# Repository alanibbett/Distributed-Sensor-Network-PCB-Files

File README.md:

# Distributed-Sensor-Network-PCB-Files
PCB files in eagle PCB format and Gerber for the sensor board of the DSN 
This repository contains the PCB design files for a simple raspberry PI expansion board. 
This design does not comply with the specifications of a RaspberryPi Hat but does support contain the following items:

*	OLED Display to indicate system status: the OLED provides a way to display a simple menu based user interface
*	RFM9x LoRa radio: Provides a network connection to LoRaWAN or other LoRa nodes
*	Global Position System GPS receiver: Allows the node to accurately collect UTC time and date as well as location information of other data captured (GPS)
*	DC power supply input connector: To supply regulated 5VDC to the system
*	LED: Status LED – shows system status at a glance
*	GPIO: 5 of the RaspberryPI GPIO pins have been broken out in a Signal-Voltage-Ground (SVG) layout for connecting to external devices. These can include relays, sensors, switches and so forth.
*	Keypad: A three button keypad for interacting with the OLED menu user interface.

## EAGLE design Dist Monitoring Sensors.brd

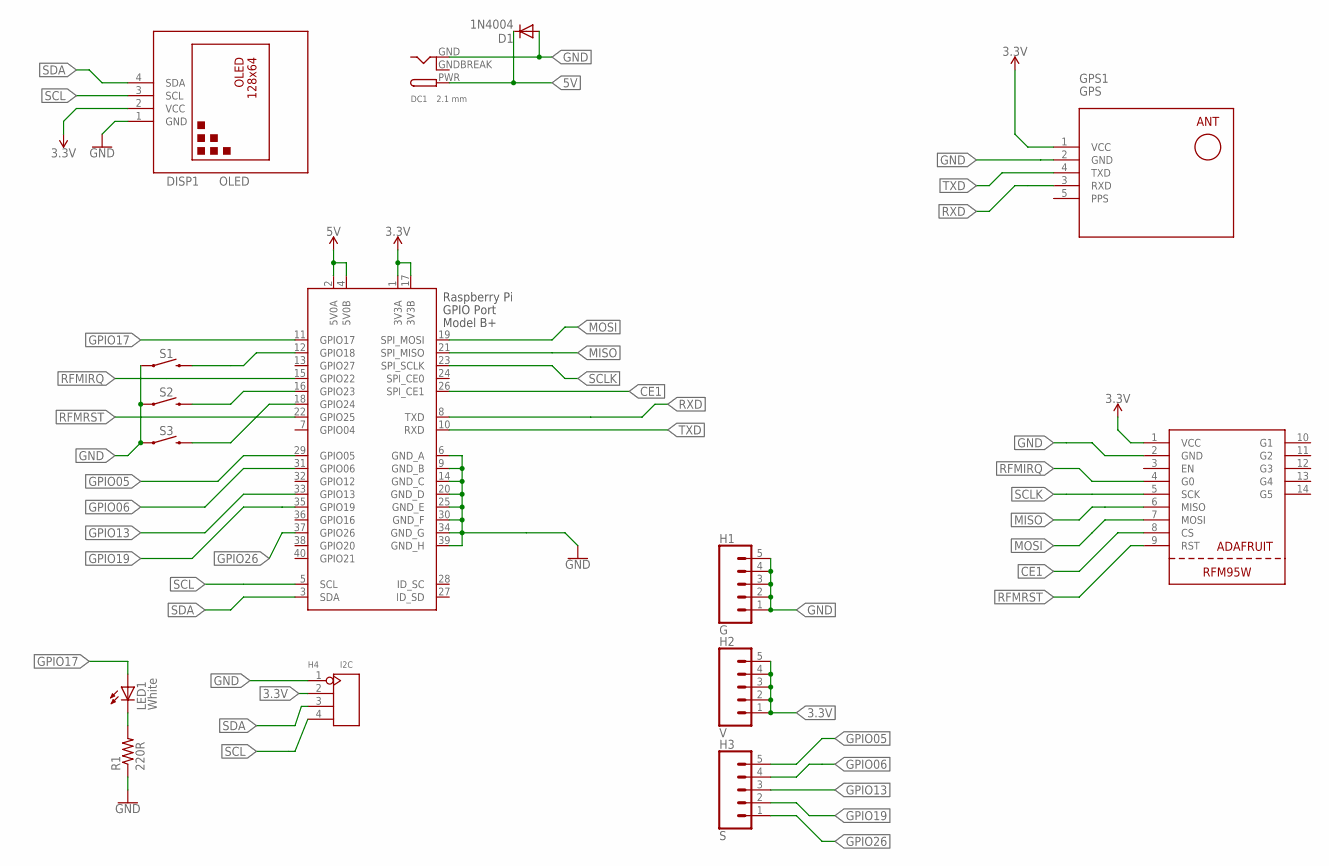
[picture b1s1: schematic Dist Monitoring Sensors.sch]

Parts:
D1: 1N4004; DO41-10
DC1: 2.1 mm; DCJACK_2MM_PTH
DISP1: OLED; DISPLAY-OLED-128X64-I2C
GPS1: GPS; GPS-RECEIVER-NEO6M-GENERIC
H1: G; 1X05
H2: V; 1X05
H3: S; 1X05
H4: I2C; H4-2.54
LED1: White; LED3MM
R1: 220R; 0207/10
S1, S2, S3: MOMENTARY-SWITCH-SPST-PTH-6.0MM; TACTILE_SWITCH_PTH_6.0MM
U1: RFM95W
X1: Raspi 40 Pin Connector; RASPI_BOARD_B+_EDGES_3DRILL_PAD

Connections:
3.3V: DISP1.2 (VCC), GPS1.1 (VCC), H2.1, H2.2, H2.3, H2.4, H2.5, H4.2, U1.1 (VCC), X1.1 (3V3A), X1.17 (3V3B)
5V: D1.C, DC1.PWR, X1.2 (5V0A), X1.4 (5V0B)
CE1: U1.8 (CS), X1.26 (SPI_CE1)
GND: D1.A, DC1.GND, DISP1.1 (GND), GPS1.2 (GND), H1.1, H1.2, H1.3, H1.4, H1.5, H4.1, R1.1, S1.1, S2.1, S3.1, U1.2 (GND), X1.6 (GND_A), X1.9 (GND_B), X1.14 (GND_C), X1.20 (GND_D), X1.25 (GND_E), X1.30 (GND_F), X1.34 (GND_G), X1.39 (GND_H)
GNDBREAK: DC1.GNDBREAK
GPIO05: H3.5, X1.29 (GPIO05)
GPIO06: H3.4, X1.31 (GPIO06)
GPIO13: H3.3, X1.33 (GPIO13)
GPIO17: LED1.A, X1.11 (GPIO17)
GPIO18: S1.3 (2), X1.12 (GPIO18)
GPIO19: H3.2, X1.35 (GPIO19)
GPIO23: S2.3 (2), X1.16 (GPIO23)
GPIO24: S3.3 (2), X1.18 (GPIO24)
GPIO26: H3.1, X1.37 (GPIO26)
MISO: U1.6 (MISO), X1.21 (SPI_MISO)
MOSI: U1.7 (MOSI), X1.19 (SPI_MOSI)
unnamed: LED1.K (C), R1.2
RFMIRQ: U1.4 (G0), X1.15 (GPIO22)
RFMRST: U1.9 (RST), X1.22 (GPIO25)
RXD: GPS1.3 (RXD), X1.8 (TXD)
SCL: DISP1.3 (SCL), H4.4, X1.5 (SCL)
SCLK: U1.5 (SCK), X1.23 (SPI_SCLK)
SDA: DISP1.4 (SDA), H4.3, X1.3 (SDA)
TXD: GPS1.4 (TXD), X1.10 (RXD)

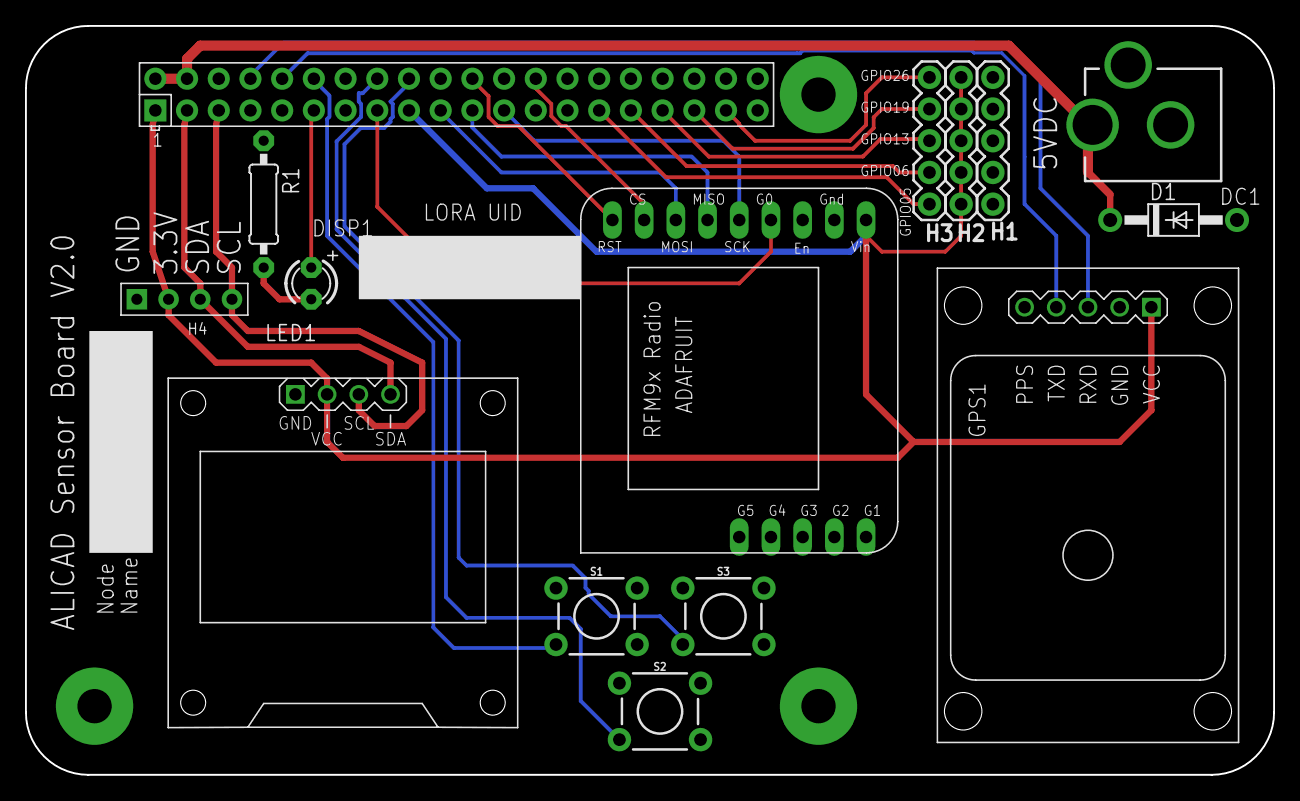
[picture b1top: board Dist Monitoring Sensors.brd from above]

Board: 2 copper layers, 100.0 x 60.0 mm, 15 parts (0 on the bottom side), 23 nets.

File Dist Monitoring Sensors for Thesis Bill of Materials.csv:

"Part";"Value";"Device";"Package";"Description";"MPN";"PROD_ID";"SF_SKU";"VALUE";
"D1";"1N4004";"1N4004";"DO41-10";"DIODE";"";"";"";"";
"DC1";"2.1 mm";"DCBARRELPTH";"DCJACK_2MM_PTH";"2.0mm DC Barrel Jack";"";"";"";"";
"DISP1";"OLED";"DISPLAY-OLED-128X64-I2C";"DISPLAY-OLED-128X64-I2C";"128x64 Dot Matrix OLED Module based on SSD1306 chip";"";"";"";"";
"GPS1";"GPS";"GPS-RECEIVER-NEO6MGENERIC";"GPS-RECEIVER-NEO6M-GENERIC";"Generic GPS Receiver Module based on NEO-6 device";"";"";"";"";
"H1";"G";"CONN_05";"1X05";"Multi connection point. Often used as Generic Header-pin footprint for 0.1 inch spaced/style header connections";"";"";"";"";
"H2";"V";"CONN_05";"1X05";"Multi connection point. Often used as Generic Header-pin footprint for 0.1 inch spaced/style header connections";"";"";"";"";
"H3";"S";"CONN_05";"1X05";"Multi connection point. Often used as Generic Header-pin footprint for 0.1 inch spaced/style header connections";"";"";"";"";
"H4";"I2C";"DIP-BLACK-MALE-HEADER-VERT(4P-2.54)";"H4-2.54";"320020017";"P125-1104A0BS116A1";"";"";"4p-2.54";
"LED1";"White";"LED3MM";"LED3MM";"LED";"";"";"";"";
"R1";"220R";"R-US_0207/10";"0207/10";"RESISTOR, American symbol";"";"";"";"";
"S1";"";"MOMENTARY-SWITCH-SPST-PTH-6.0MM";"TACTILE_SWITCH_PTH_6.0MM";"Momentary Switch (Pushbutton) - SPST";"";" SWCH-08441";"COM-00097";"";
"S2";"";"MOMENTARY-SWITCH-SPST-PTH-6.0MM";"TACTILE_SWITCH_PTH_6.0MM";"Momentary Switch (Pushbutton) - SPST";"";" SWCH-08441";"COM-00097";"";
"S3";"";"MOMENTARY-SWITCH-SPST-PTH-6.0MM";"TACTILE_SWITCH_PTH_6.0MM";"Momentary Switch (Pushbutton) - SPST";"";" SWCH-08441";"COM-00097";"";
"U1";"RFM95W";"RFM95W";"RFM95W";"Adafruit LORA Packet Radio";"";"";"";"";
"X1";"Raspi 40 Pin Connector";"RASPI_BOARD_B+#_E3P";"RASPI_BOARD_B+_EDGES_3DRILL_PAD";"Raspberry Pi GPIO connector with markings for the outer dimensions of the Raspberry Pi board model B+";"";"";"";"";

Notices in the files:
parts and their libraries:
SparkFun-Switches: Licensing: Creative Commons ShareAlike 4.0 International - https://creativecommons.org/licenses/by-sa/4.0
